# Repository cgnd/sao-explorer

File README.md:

---
typora-copy-images-to: ./images
---

# SAO Explorer v1

The SAO Explorer v1 is a [Simple Add-on](https://hackaday.io/project/175182-simple-add-ons-sao) (SAO) board that breaks out the 2x3 0.100" (2.54mm) SAO v2 header into a [mikroBUS](https://www.mikroe.com/mikrobus) socket and a couple SparkFun [Qwiic](https://www.sparkfun.com/qwiic) connectors. This makes it really easy to connect hundreds of different I2C breakout boards to a SAO host board—like a [Supercon badge](https://hackaday.com/2023/10/18/2023-hackaday-supercon-badge-welcome-to-the-vectorscope/)!—by quickly plugging in [MikroE Click](https://www.mikroe.com/click?interface*=i2c,i2c), [SparkFun Qwiic](https://www.sparkfun.com/categories/399), or [Adafruit STEMMA QT](https://www.adafruit.com/category/620) boards. No soldering required!

It also has a 2x5 0.050" (1.27mm) socket that allows a [Binho Nova](https://binho.io/products/usb-host-adaptor?variant=14141584343095) Multi-Protocol USB Host Adapter to be used as an I2C controller (instead of a badge). The [Binho Mission Control Software](https://support.binho.io/getting-started/binho-mission-control/download-and-installation) provides an easy-to-use GUI interface for quickly testing out new I2C devices without having to write a single line of code.

Entry for the [Supercon 8 - Add On Contest](https://hackaday.io/contest/197237-supercon-8-add-on-contest): https://hackaday.io/project/198465-sao-explorer

## Pinout Decoder Ring

The I2C and GPIO1/2 pins on the SAO connector are directly connected to the I2C, INT, and RST pins on the mikroBUS socket.

By default, the Binho Nova is connected to the I2C, INT, RST, and PWM pins on the mikroBUS socket. However, by changing a couple jumper resistors on the back of the board, the Binho Nova can be connected to the UART or SPI pins on the mikroBUS socket instead.

| SAO Connector Pin | mikroBUS socket | Binho Nova Socket                                    |
| ----------------- | --------------- | ---------------------------------------------------- |
| I2C SCL           | I2C SCL         | IO2/SCL/POCI/MISO *(populate R2, depopulate R9)*     |
| I2C SDA           | I2C SDA         | IO0/SDA/CS0/INT0 *(populate R1, depopulate R5)*      |
| GPIO1             | INT             | IO1/DAC/CS1/INT1 *(populate R6, depopulate R4)*      |
| GPIO2             | RST             | IO3/RX/SCK *(populate R26, depopulate R7, R10)*      |
| (not connected)   | PWM             | IO4/TX/PICO/MOSI *(populate R27, depopulate R3, R8)* |
| (not connected)   | AN              | IO1/DAC/CS1/INT1 *(populate R4, depopulate R6)*      |
| (not connected)   | UART TX         | IO3/RX/SCK *(populate R7, depopulate R10, R26)*      |
| (not connected)   | UART RX         | IO4/TX/PICO/MOSI *(populate R8, depopulate R3, R27)* |
| (not connected)   | SPI SCK         | IO3/RX/SCK *(populate R10, depopulate R7, R26)*      |
| (not connected)   | SPI POCI (MISO) | IO2/SCL/POCI/MISO *(populate R9, depopulate R2)*     |
| (not connected)   | SPI PICO (MOSI) | IO4/TX/PICO/MOSI *(populate R3, depopulate R8, R27)* |
| (not connected)   | SPI CS          | IO0/SDA/CS0/INT0 *(populate R5, depopulate R1)*      |

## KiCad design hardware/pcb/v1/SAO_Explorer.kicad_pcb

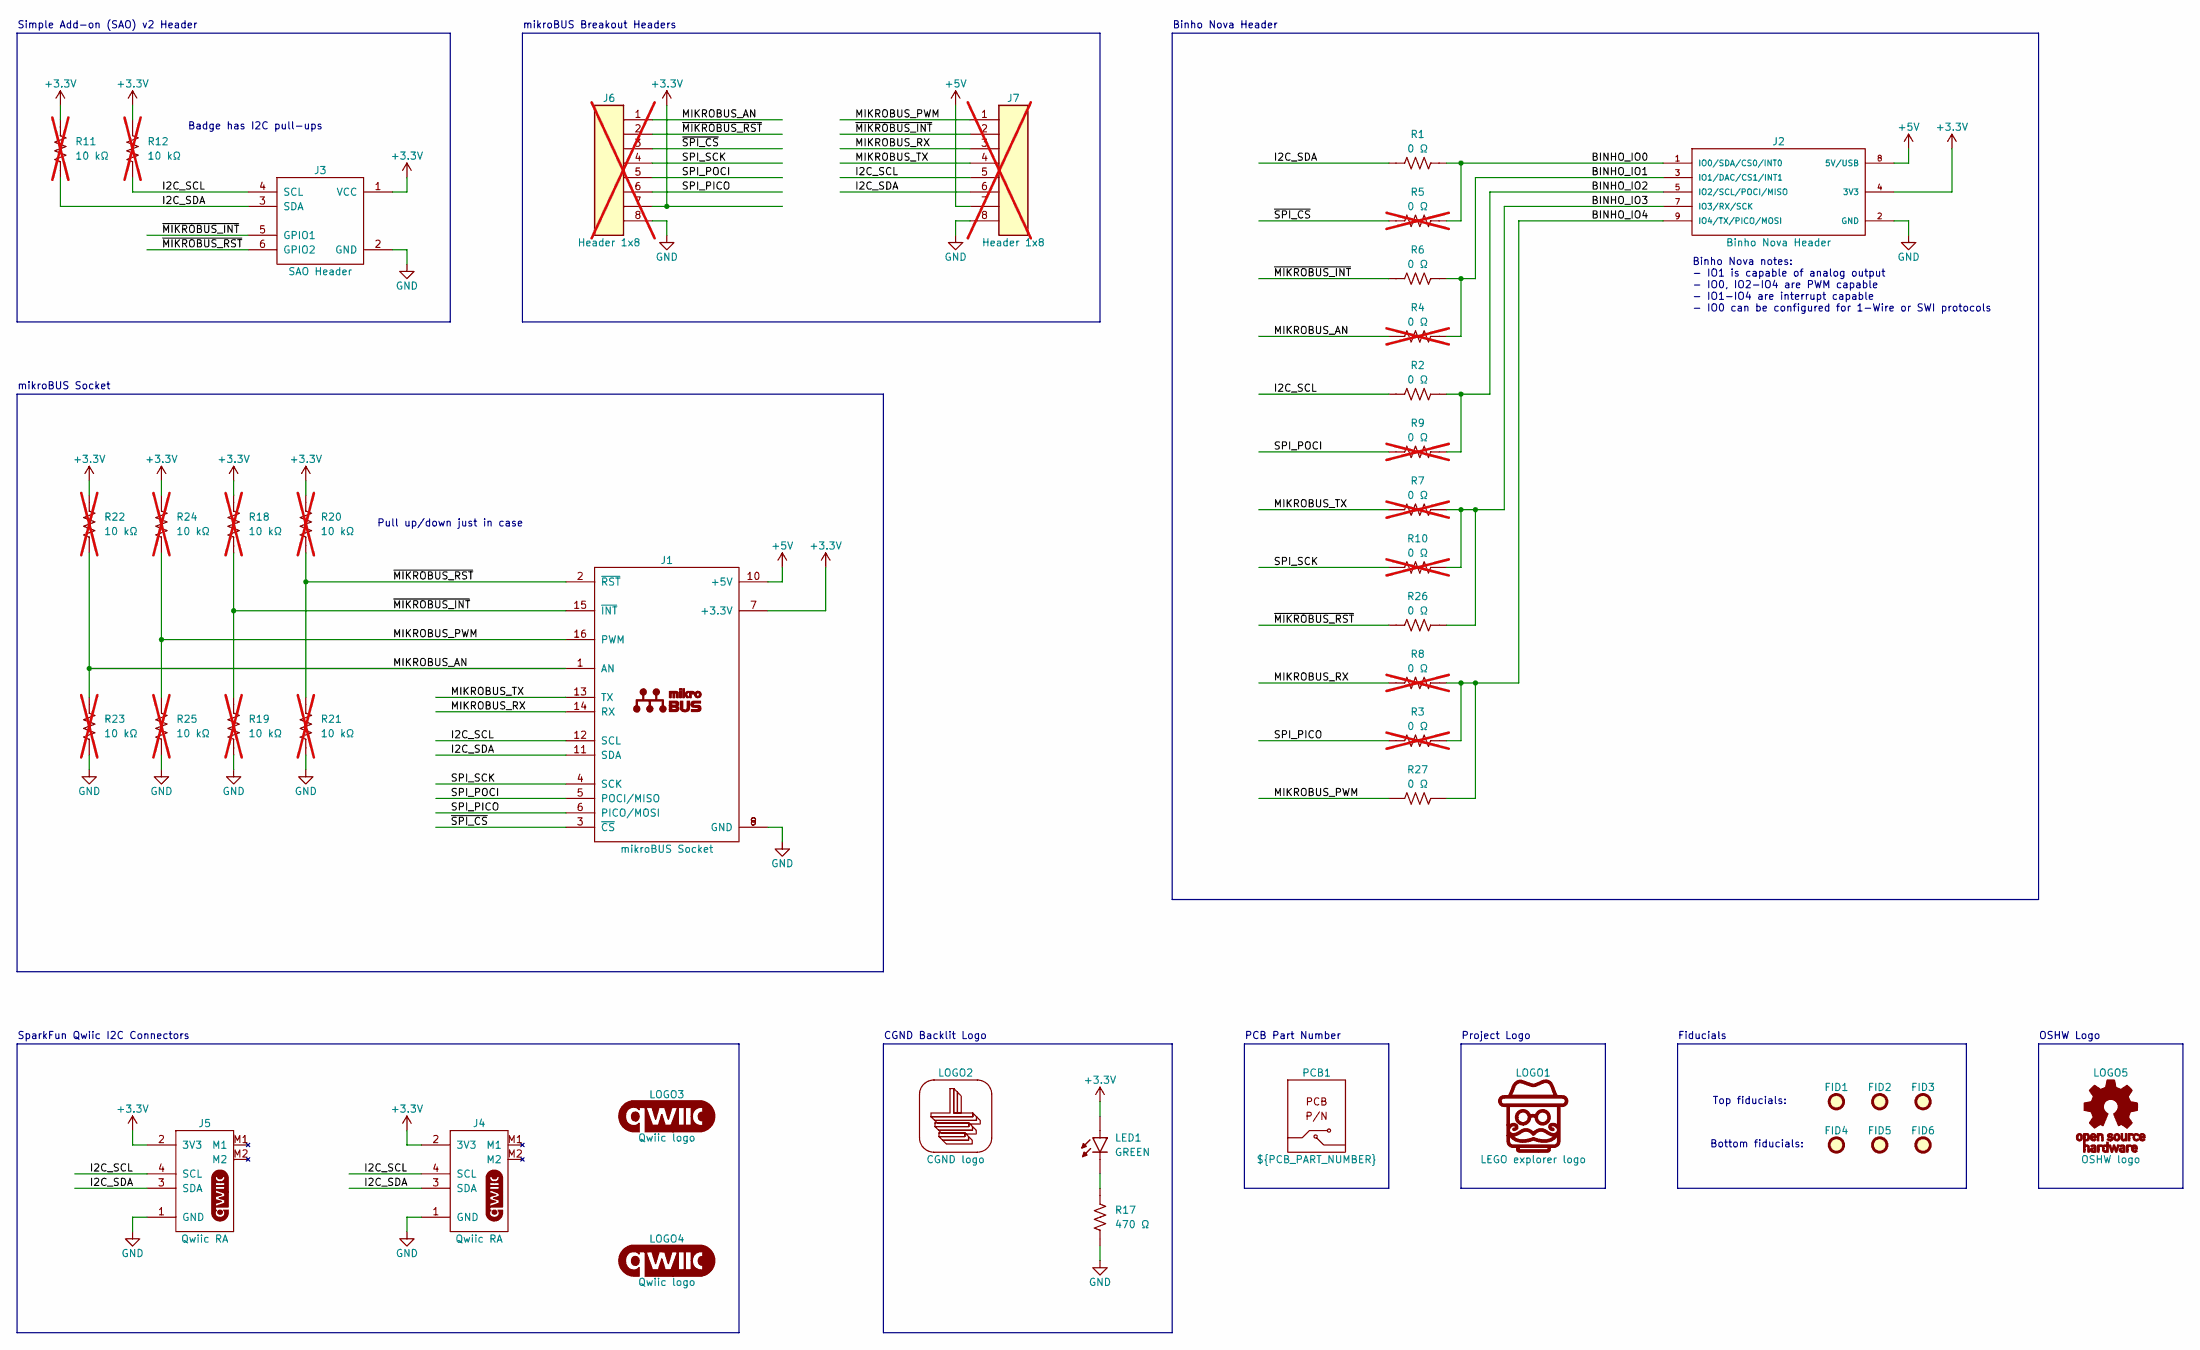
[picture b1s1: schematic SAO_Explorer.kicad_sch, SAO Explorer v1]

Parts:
FID1, FID2, FID3, FID4, FID5, FID6: Fiducial; FIDC50M100K100L
J1: mikroBUS Socket; MIKROE_MIKROE-4248; Manufacturer Part Number MIKROE-4248
J2: Binho Nova Header; SAMTEC_SHF-105-01-x-D-SM; Manufacturer Part Number SHF-105-01-L-D-SM-K-TR
J3: SAO Header; SHDRV6W64P254_3X2_1512X910H910_SAO_V2; Manufacturer Part Number SBH11-NBPC-D03-ST-BK
J4, J5: Qwiic RA; JST_SM04B-SRxS; Manufacturer Part Number SM04B-SRSS-TB(LF)(SN)
J6, J7: Header 1x8; HDRV8W67P254_8X1_2032X241H858; Manufacturer Part Number 68001-208HLF; not fitted
LED1: GREEN; SUNLED_XZVG45WT-9_CGND_LOGO; Manufacturer Part Number XZVG45WT-9
LOGO1: LEGO explorer logo; LOGO_LEGO_EXPLORER_OUTLINE_500X500_SILKSCREEN
LOGO2: CGND logo; LOGO_CGND_500X500_BACKLIT
LOGO3, LOGO4: Qwiic logo; LOGO_SPARKFUN_QWIIC_500X160_SILKSCREEN
LOGO5: OSHW logo; LOGO_OSHW_570X600_SILKSCREEN
PCB1: ${PCB_PART_NUMBER}; Manufacturer Part Number ${PCB_PART_NUMBER}
R1, R2, R6, R26, R27: 0 Ω; RESC160X80X55L25N; Manufacturer Part Number RC0603JR-070RL
R3, R4, R5, R7, R8, R9, R10: 0 Ω; RESC160X80X55L25N; Manufacturer Part Number RC0603JR-070RL; not fitted
R11, R12, R18, R19, R20, R21, R22, R23, R24, R25: 10 kΩ; RESC160X80X55L25N; Manufacturer Part Number RC0603JR-0710KL; not fitted
R17: 470 Ω; RESC160X80X55L25N; Manufacturer Part Number RC0603JR-07470RL

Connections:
+3.3V: J1.7 (+3.3V), J2.4 (3V3), J3.1 (VCC), J4.2 (3V3), J5.2 (3V3), J6.7, LED1.A (Anode), R11.2, R12.2, R18.2, R20.2, R22.2, R24.2
+5V: J1.10 (+5V), J2.8 (5V/USB), J7.7
/BINHO_IO0: J2.1 (IO0/SDA/CS0/INT0), R1.2, R5.2
/BINHO_IO1: J2.3 (IO1/DAC/CS1/INT1), R4.2, R6.2
/BINHO_IO2: J2.5 (IO2/SCL/POCI/MISO), R2.2, R9.2
/BINHO_IO3: J2.7 (IO3/RX/SCK), R7.2, R10.2, R26.2
/BINHO_IO4: J2.9 (IO4/TX/PICO/MOSI), R3.2, R8.2, R27.2
/I2C_SCL: J1.12 (SCL), J3.4 (SCL), J4.4 (SCL), J5.4 (SCL), J7.5, R2.1, R12.1
/I2C_SDA: J1.11 (SDA), J3.3 (SDA), J4.3 (SDA), J5.3 (SDA), J7.6, R1.1, R11.1
/MIKROBUS_AN: J1.1 (AN), J6.1, R4.1, R22.1, R23.2
/MIKROBUS_PWM: J1.16 (PWM), J7.1, R24.1, R25.2, R27.1
/MIKROBUS_RX: J1.14 (RX), J7.3, R8.1
/MIKROBUS_TX: J1.13 (TX), J7.4, R7.1
/SPI_PICO: J1.6 (PICO/MOSI), J6.6, R3.1
/SPI_POCI: J1.5 (POCI/MISO), J6.5, R9.1
/SPI_SCK: J1.4 (SCK), J6.4, R10.1
/~MIKROBUS_INT: J1.15 (~INT), J3.5 (GPIO1), J7.2, R6.1, R18.1, R19.2
/~MIKROBUS_RST: J1.2 (~RST), J3.6 (GPIO2), J6.2, R20.1, R21.2, R26.1
/~SPI_CS: J1.3 (~CS), J6.3, R5.1
GND: J1.8 (GND), J1.9 (GND), J2.2 (GND), J2.6 (GND), J2.10 (GND), J3.2 (GND), J4.1 (GND), J5.1 (GND), J6.8, J7.8, R17.1, R19.1, R21.1, R23.1, R25.1
unnamed: LED1.C (Cathode), R17.2

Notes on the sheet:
Simple Add-on (SAO) v2 Header
PCB Part Number
Bottom fiducials:
CGND Backlit Logo
Badge has I2C pull-ups
Project Logo
SparkFun Qwiic I2C Connectors
Binho Nova Header
Binho Nova notes: - IO1 is capable of analog output - IO0, IO2-IO4 are PWM capable - IO1-IO4 are interrupt capable - IO0 can be configured for 1-Wire or SWI protocols
Top fiducials:
Fiducials
mikroBUS Breakout Headers
mikroBUS Socket
OSHW Logo
Pull up/down just in case

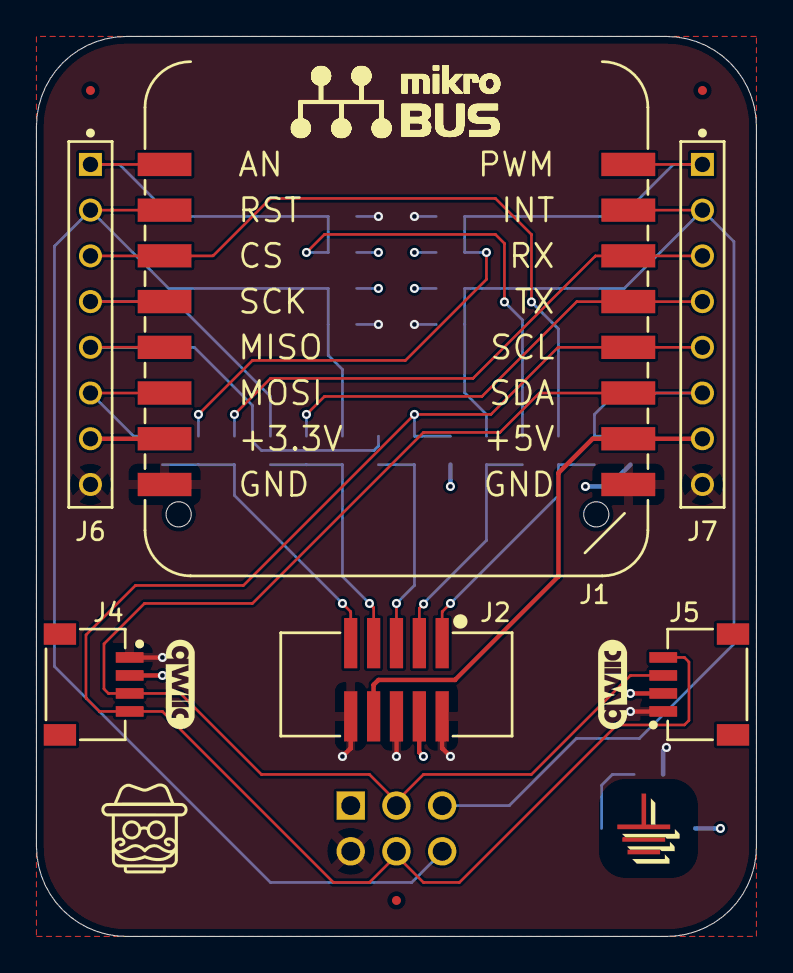
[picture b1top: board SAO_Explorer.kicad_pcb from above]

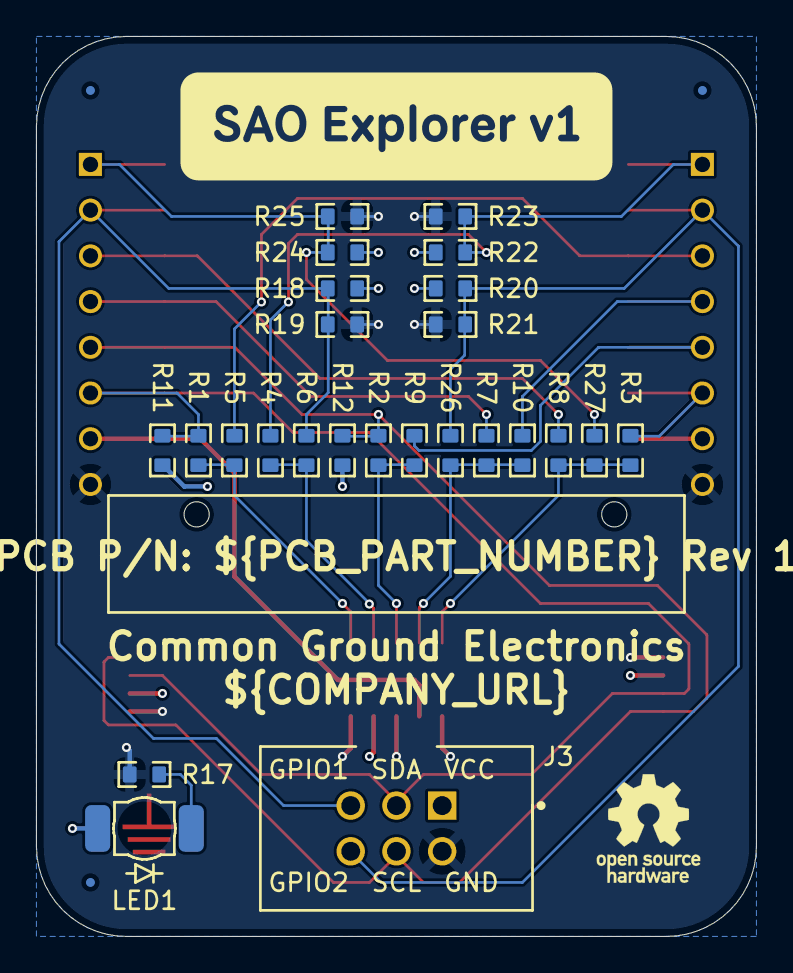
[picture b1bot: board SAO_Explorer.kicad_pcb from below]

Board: 4 copper layers, 40.0 x 50.0 mm, 42 parts (29 on the bottom side), 21 nets.

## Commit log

2024-10-15 Add 100078 Rev 1 schematic and layout
2024-10-15 Fix typos in README
2024-10-15 Fix schematic net label formatting
2024-10-15 Update schematic export settings
2024-10-26 Add hackaday.io project link

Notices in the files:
hardware/pcb/v1/SAO_Explorer.kicad_pcb:
SPDX-License-Identifier: ${SPDX_LICENSE_ID}
SPDX-FileCopyrightText: © ${COPYRIGHT_HOLDER}
parts and their libraries:
SPDX_LICENSE_ID: CERN-OHL-P-2.0
